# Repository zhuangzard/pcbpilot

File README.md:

<h1 align="center">pcbpilot</h1>

<p align="center">
  让 AI 直接操作嘉立创 EDA 专业版：读数据手册、画原理图、布局 PCB、整理丝印并完成检查。
</p>

<p align="center">
  <a href="https://github.com/zhuangzard/pcbpilot"><b>GitHub</b></a> ·
  <a href="docs/manual.md"><b>使用手册</b></a> ·
  <a href="docs/quick-start.md"><b>快速开始</b></a> ·
  <a href="README.en.md">English</a>
</p>

> **致谢与来源**：pcbpilot 由 [zhoushoujianwork/easyeda-agent](https://github.com/zhoushoujianwork/easyeda-agent)
> 分叉发展而来。CLI、daemon、连接器、typed action 体系、Skill、块库和大部分文档都出自原项目，
> 原作者与所有贡献者的提交历史完整保留在本仓库中，许可证为 MIT。衷心感谢原作者的工作。
> pcbpilot 在此基础上独立演进（首个新增能力是 `pcb auto` 电气感知整板自动设计引擎），
> 使用独立的命令名、端口段（61832–61841）、插件 uuid 与更新渠道，可与原版同时安装。

`pcbpilot` 是 EasyEDA Pro（嘉立创 EDA 专业版）的 AI 自动化层。你可以直接描述想做的
电路或要修的问题，Agent 会读取真实工程数据，通过官方 `eda.*` API 完成操作，并在写入前后
检查器件身份、引脚网络、几何、DRC 和保存状态。支持 **V3（3.2.x）与 V4**、桌面版与 Web 版、
国际版（pro.easyeda.com）与国内版（lceda.cn）。

## 它能做什么

| 使用场景 | 能力 |
|---|---|
| **拿 PDF / 尺寸图建库** | 读取型号、引脚和封装证据，创建 Symbol、Footprint、Device 和可选 3D Model；校验来源、焊盘依据和 pin↔pad 映射。[实战：AS07 私有库与框外丝印](docs/examples/as07-m1101d-sma/README.md) |
| **从需求做到一块板** | 从自然语言需求完成选型、原理图、分区布局、PCB、板框、叠层、布线、铺铜、丝印、DRC 和制造检查 |
| **原理图器件标准化** | 用 LCSC C 号或准确型号替换非标准器件，保留位号、位置和 PCB 同步身份；报告引脚差异并指导重新接线 |
| **原理图整理与修复** | 读取完整连接图，检查悬空、短路、跨页网名、NC、位号和模块归属，重新排版并回读验证 |
| **PCB 布局与布线** | `pcb auto` 整板引擎：机械约束 → 最小可行板框 → 原理图模块归属驱动的布局 → 多层协商布线 → 电源平面/分区铺铜 → 独立 DRC；天线净空、孔距、差分对、开关电源热回路 |
| **丝印调整** | 自动避开焊盘、器件体、禁区、板框和其他标签；添加板注、接口名、LED 极性及 SVG Logo |
| **复用成熟电路** | 从内置电路块库复用 CH340、ESP32 自动下载、按键、USB Hub、降压等拓扑，放件、连线并对账 |
| **电气分析与设计意图（v0.5）** | 从原理图做直流电源仿真（每脚电流、稳压器工作点、纹波），推导每个功能块的用途、每个网的电压/电流/线宽/过孔/间距/阻抗和网络类，写进 EasyEDA 规则与原理图注释；高压按 IEC 62368-1 / 60601-1（MOOP/MOPP）/ 61010-1 算爬电、间隙与开槽 |
| **检查与交付** | 原理图连接与几何检查、PCB DRC/DFM、BOM、网表、制造文件、截图、审计日志和显式保存；**每次运行自动生成版本化的设计报告**（仿真图表、器件可行性、工程计算、测试点、制造与上电注意事项），可直接交付客户 |

完整能力与状态见 [功能清单](docs/FEATURES.md)，命令索引见
[原理图 CLI](docs/cli/schematic.md) 和 [PCB CLI](docs/cli/pcb.md)。

## v0.5：从原理图到交付报告的电气闭环

以前原理图到 PCB 之间只传“位置”，PCB 不知道每个电路是做什么的、流多大电流、要多高的安规。
v0.5 把原理图里的电气意图算出来，一路带到布线、检查和交付：

```text
原理图 ──▶ sim power（直流仿真）──▶ intent derive（设计意图）──┬─▶ sch intent-annotate（写回原理图注释）
                                                             ├─▶ pcb rules apply（写入 EasyEDA 网络类/线宽/间距/差分对规则）
                                                             └─▶ pcb auto run --intent --sim
                                                                   ├─ 按段电流定线宽、布线后 IR 压降校核
                                                                   ├─ 高压：按标准的爬电/间隙、隔离带、自动开槽
                                                                   ├─ 高速：阻抗、对内/组内等长、参考平面
                                                                   └─ feedback.json：布线难点回推原理图（换脚等）
                                                                            ──▶ report design（版本化设计报告）
```

```bash
pcbpilot sim power      --project <工程> --pages <p1>,<p2> --out sim.json --report sim.md
pcbpilot intent derive  --project <工程> --pages <p1>,<p2> --out intent.json --report-dir reports/<项目>
pcbpilot sch intent-annotate --project <工程> --page <p1> --intent intent.json
pcbpilot pcb rules apply --project <工程> --doc <PCB> --intent intent.json      # 先 --dry-run
pcbpilot pcb auto run --board board.json --intent intent.json --sim sim.json --place --report-dir reports/<项目>
```

2026-09-27 这条链在 EasyEDA 桌面版 V3 上对 ESP32-S3 四层板完整实跑：规则写入并保存重载后仍同步，
布线 30/30、平面连接 52/52、各电源轨 IR 压降在预算内，原生 DRC 通过。高压（反激、医疗 2×MOPP、
CAT III 600 V、400 V 逆变）与高速（USB3、HDMI、PCIe、千兆以太网、DDR）压力测试的现状与已知缺口见
[高压隔离](.agents/skills/pcbpilot/references/recipes/hv-isolation.md) 与
[高速](.agents/skills/pcbpilot/references/recipes/high-speed.md) 配方。

### v0.6：设计前仿真 + 设计后仿真 + 板边安全距离

- **设计前**：`sim power`（电源树直流仿真）、`sim analog`（模拟电路 ngspice 仿真并按结果改元件值，改值需确认）、
  `intent derive`（线宽、**按电流定尺寸与数量的过孔**、间距、阻抗、**板边安全距离**）。
- **设计后**：`sim post-layout` 在 EasyEDA 回读的**真实铜皮**上算每个负载脚的直流压降、每个过孔电流、电流密度、
  每层稳态温度图和器件板温，并给出该加宽的线段、拐角与过孔（手工布的板也能用）；可选 Elmer FEM 交叉校验。
- **板边安全距离**（所有板默认）：外层铜 ≥ 0.5 mm、内层平面 ≥ 0.76 mm，高压域按爬电/间隙；写入 EasyEDA 规则并由
  `pcb check` 按 ERROR 检查。安装 pcbpilot 时自动安装 ngspice 与 Elmer（`pcbpilot sim tools`）。

### v0.7：console 本地驾驶舱、美观度测量、核心安全修复

daemon 在 `http://127.0.0.1:61832/ui/` 提供本地网页（`pcbpilot console open`，令牌在 `~/.pcbpilot/console.token`，仅回环）：
**监控首页**实时显示 daemon（pid/运行时长/端口/自动保存/登录服务）、各组件版本对齐（CLI、Skill、MCP、每个窗口的 connector）、
EasyEDA 窗口、**系统做过的全部项目**（运行中/空闲/已结束、DRC 与报告结论、时长、最后错误，重启后保留）和实时动作流；
项目页有设计流程时间线（S0–P11，证据视图）、仿真轮次与差值、报告预览、资料库（拖放上传 + BM25 检索，`pcbpilot kb`）、
流程配置（`pcbpilot.project.json`，`pcbpilot project-config`，Skill 先读、跳过项写进报告）；`pcbpilot ask` 决策卡在页面上回答。
console 从不编辑 EDA 工程，写入仍只走 typed action。本地 Agent（Claude Code / Codex）桥接是 v0.8 计划。
设计与 API 见 [docs/console-design.md](docs/console-design.md)。

同版还有：`pcbpilot pcb aesthetics` 布局/布线美观度测量（含对称检测与风格档位，只报告不计分，排在安全/电气之后）；
核心修复——按电流的过孔阵列在每个换层处强制满足（不满足必报）、差分对成对布线与耦合/过孔对称检查、布局给差分对留通道、
隔离/爬电/板边/过孔这些安全修复不再受时间预算影响（做不到就判 **NOT DELIVERABLE** 并写明原因）、守护进程重启更可靠。

### v0.7.1：美观度生成（PCB + 原理图）与原生总线

PCB 布局美观阶段（对齐、朝向、等距、同构子电路对称复制，布线复核守护）与布通后美化（扇出射线化、入线沿焊盘轴、S 形消除、落格）；
原理图走线清理、长线改标签、虚拟总线泳道与**原生总线**（宿主只接受 `NAME[a:b]`，只画带序号的组，V3 3.2.149 现场验证）；
美观交换有界且必报（每项电气分 ≤0.5、布局最多 +1 过孔），安全/布通/DRC/问题条数零容忍；`project inspect-eprj3`、
`health.officialCli`、`api upstream-diff` 吸收嘉立创官方 CLI 的格式与 API 知识。

### 设计报告（每次运行自动更新，版本化交付客户）

`report design` 按固定模板生成单文件 HTML（图表内联，可离线打开、打印）+ Markdown + JSON，每次运行一个新版本
`reports/<项目>/vN/`，并写出与上一版的变化。章节：封面与总体结论 · 执行摘要与主要风险 · 设计意图 ·
电源仿真（各场景电流、功率平衡、电源树、稳压器工作点、纹波、模型可信度）· **器件可行性**（每个器件的
电压/电流/功率 vs 额定与余量，未知额定标“需数据手册”，不猜）· 工程计算（线宽、过孔、间距、阻抗、爬电，
附公式）· 布局与布线（截图、IR 压降、SI、隔离、回推建议）· 验证状态 · **测试点计划**（测哪里、期望值
± 公差、仪器与方法）· **制造与装配注意事项** · **上电调试流程** · 附录。

样例（今天 ESP32 现场实跑数据生成）：[v1 报告（Markdown）](docs/examples/esp32-mini-design-report/v1/report.md) ·
[单文件 HTML（下载后打开）](docs/examples/esp32-mini-design-report/v1/report.html) ·
[v1→v2 变更记录](docs/examples/esp32-mini-design-report/CHANGELOG.md) ·
模板与每节计算来源：[templates/design-report](.agents/skills/pcbpilot/templates/design-report/README.md) ·
使用说明：[design-report.md](.agents/skills/pcbpilot/references/design-report.md)。

## 直接这样告诉 Agent

安装完成后，不需要先学习 CLI。把需求和必要的文件交给支持 Skill 的 Agent，并明确使用
`pcbpilot`。

### 用 PDF 创建器件库

```text
请使用 pcbpilot，根据附件 ABC123.pdf 为完整型号 ABC123-QFN 建库。
先检查 EasyEDA 和 LCSC 库是否已有完全匹配的器件；没有再通读整份数据手册，核对订购
后缀、引脚表、封装尺寸图和推荐焊盘。自动创建 Symbol、Footprint 和 Device，保留证据页码，
先运行离线规格校验，再写入个人库。完成后回读 pin↔pad 映射并放置一个实例检查 Pin-1。
只有手册确实存在多个无法消歧的封装或缺少关键尺寸时再问我。
```

这个流程使用 `pcbpilot lib device validate --spec …` 在打开或修改 EasyEDA 前检查数据手册
证据、几何和引脚映射，再由 `lib device build` 创建完整资产。规格契约见
[数据手册驱动的自动建库](.agents/skills/pcbpilot/references/library-authoring.md)。

### 做一块 ESP32 最小系统板

```text
请使用 pcbpilot，在项目 ceshi 中完成一块 ESP32-S3-WROOM-1 最小系统板：
5V 端子输入，降压到 3V3，CH340 USB 下载，BOOT/RESET 按键，一颗 GPIO 控制的 LED，
四角 M3 固定孔。做 4 层板，GND 内电层，模组天线区域所有层 keepout。
请自行选型并核对数据手册，从原理图、布局、布线、铺铜、丝印一直做到 DRC 和保存完成。
```

完整实战与真实截图见
[一份需求文档 → ESP32-S3 四层板](docs/showcase-esp32-mini.md)。

### 调整当前 PCB 的丝印

```text
请使用 pcbpilot 检查当前 PCB 的全部位号和自由丝印。把压焊盘、超板框、重叠、
朝向不一致和底层未镜像的问题整理好；保留 LED 正负极、接口名称和必要板注。
完成后运行 pcb check 和官方 DRC，导出一张复核图并保存。
```

### 标准化原理图器件

```text
请使用 pcbpilot 扫描当前原理图，把无准确料号、非标准符号或封装不一致的器件列出来。
优先匹配标准器件库和准确 LCSC C 号，核对型号、封装及引脚后再替换。
替换时保留位号、位置和 uniqueId；如果 pinDiff 非空，修复接线并重新运行 sch check、
bridge-check 和官方 DRC。最后输出替换清单和仍无法确定的器件。
```

### 出一份交付客户的设计报告

```text
请使用 pcbpilot 给当前工程出设计报告：先对原理图做电源仿真和设计意图推导，再用已完成的布线结果、
保存重载后的回读、原生 DRC、pcb check、规则同步和逐焊盘对账作为证据，生成新版本的设计报告。
额定未知的器件标“需数据手册”，不要猜；总体结论里的每条警告写明取舍，告诉我相对上一版改了什么。
```

### 检查并修复已有工程

```text
请使用 pcbpilot 全面检查当前原理图和 PCB。先读取真实器件、引脚、网络、板框、叠层和
DRC 规则，再修复可以确定的问题。不要凭截图猜连接；所有修改完成后回读对账、运行连接/几何/DRC 检查、
保存，并把仍需人工决策的问题单独列出。
```

## 效果展示

### ESP32-S3 四层板：一句需求交给新 Agent，到 DRC 通过（v0.3.0，2026-09-25 实测）

输入只有 [esp32MiniRequire.md](esp32MiniRequire.md) 第一节的客户原始需求（不给 BOM、不给网表），交给一个
**没有任何上下文的新 Agent**，约 36 分钟自行完成：

- **原理图**：自行选型，画两页原理图（31 个器件、21 个网络，按功能模块加框），回读逐脚 0 差异，两页 strict gate 通过；
- **布局**：`pcb auto` 求出 53.5 × 39.5 mm 的最小板框，四角 M3，ESP32 天线独占上边并全层禁布，USB-C 贴下边外伸
  0.5 mm；原理图模块框决定 PCB 归属（降压电容跟降压芯片、EN 复位电容贴 EN 脚、ESD 贴 USB 口）；两轮自检
  （第 2 轮保存 → 重载 → 重读 → 重新出图）后进入布线；
- **布线**：4 层（TOP / IN1 GND 平面 / IN2 电源分区 / BOTTOM），信号 30/30、平面连接 54/54，综合分 92.3；
  原生 DRC 通过、`pcb check` 0 ERROR、丝印无重叠、逐焊盘对账 0 差异、保存重开后内容哈希不变；
- **反哺工具**：这一轮暴露的 11 个问题（USB-C 封装定位孔未建模、USB 差分线跨电源分割、丝印不收敛、
  按工程名检查误报等）全部修进仓库，并在同一块板上现场复测通过，随 v0.3.0 发布；
- 宿主：EasyEDA Pro **V3 3.2.149 桌面版**（国际版）。

| 原理图第 1 页（USB-C / CH340C 串口与自动下载 / 5V 输入） | 原理图第 2 页（降压 / ESP32-S3 / 按键 / LED） |
|---|---|
|  |  |

| 布局（两轮自检后、布线前） | 布线 + 铺铜 + 丝印（终检通过） |
|---|---|
|  |  |

过程、问题与修法见 [pcb-auto 实测记录](.agents/skills/pcbpilot/references/pcb-auto.md#实测记录)。

## 上游 easyeda-agent 的案例（分叉前）

以下三个案例由原项目作者 [zhoushoujian](https://github.com/zhoushoujianwork) 在分叉前完成，保留在此作为能力来源的记录。

### 从模块尺寸图到个人私有库

**需求：** 按用户提供的 AS07-M1101D-SMA 尺寸与引脚图创建个人库，原理图保持双排引脚的
左右顺序；封装标注引脚名和型号，丝印全部放在模块覆盖区域外，安装后仍可查看，并收紧、对齐。

**结果：** 已创建并保存 Symbol、Footprint 和 Device，核对 8 个引脚与 8 个通孔焊盘映射；
修正符号边框闭合和引脚方向。封装左侧用两列脚号＋名称，列间距约 0.5 mm，靠框一列距框
约 0.6 mm；型号居中放在框外上方，实际文字包围盒回读无重叠。
最终按用户要求使用普通引脚线和未定义类型，1 脚使用独立圆形标记；保留用户清理 NC 后的状态。

这次输入是用户尺寸图，不是完整原厂 PDF；焊盘与部分偏移采用明确假设计算。
尚未验证实物装配、放置实例和 PCB DRC，不作为生产就绪证明。
[查看原始需求图、封装预览、规格与回读结果](docs/examples/as07-m1101d-sma/README.md)。

### 嘉立创 PCB 初级考试第十八期：AT32F415 Layout

当前参数化 Layout 基线包含 69 个器件、15 个功能区和 90 × 50 mm 圆角板框，用于验证
“样例关系 → 算法候选 → AI 选择 → typed 写入 → 回读”的布局方法。该图展示布局阶段结果，
不代表整板布线或生产检查已经完成。

标准考试来源：**嘉立创 PCB 初级考试题第十八期**。执行步骤、参数和验证边界见
[260919 AT32F415 考试执行指导](docs/260919-exam-execution-guide.md)。

### 数据驱动的原理图组合

Agent 先在本地连接数据中核对器件、引脚和网络，再计算模块内部布局并写回 EasyEDA；粉色虚线框
表示独立功能区，Apply 后逐脚回读，而不是仅凭截图判断成功。

## 安装与开始使用

pcbpilot 由四部分组成：`pcbpilot` CLI/daemon、运行在 EasyEDA 内的 **PCB Pilot Connector**
（`.eext`，侧载安装，不在插件市场）、AI 客户端里的 `pcbpilot` Skill，以及可选的 MCP 服务。

### 新机器：一句话交给 Claude

```text
克隆 https://github.com/zhuangzard/pcbpilot 并按仓库 AGENTS.md 的「新机器安装」完成 pcbpilot 安装，
最后告诉我需要我手动做的连接器导入步骤。
```

Agent 会运行 [`scripts/setup-agent.sh`](scripts/setup-agent.sh)：编译 CLI，为 **Claude Code / Codex / ZCode**
链接 Skill 并注册 MCP，构建连接器，把 daemon 装成开机登录自动启动的服务（必需，`pcbpilot daemon service install`），最后自动验证（MCP 真实握手）。若机器上装过上游
easyeda-agent，会移除其 MCP 并把其 Skill 移入可恢复的备份，避免与 pcbpilot 争用同类任务。也可以自己运行：

```bash
git clone https://github.com/zhuangzard/pcbpilot.git && cd pcbpilot
scripts/setup-agent.sh          # --dry-run 先预览；无 Go 时自动改用发布版
```

只装已发布版本（无需克隆）：

```bash
curl -fsSL https://raw.githubusercontent.com/zhuangzard/pcbpilot/main/install.sh | bash      # macOS / Linux
irm https://raw.githubusercontent.com/zhuangzard/pcbpilot/main/install.ps1 | iex             # Windows PowerShell
```

三种安装方式都会顺带执行 `pcbpilot sim tools install --yes`，自动安装开源仿真工具：**ngspice**（必需，
`sim power --spice-check` 与模拟 SPICE 流程）和 **Elmer FEM**（可选热交叉验证；macOS 走官方 Homebrew tap
源码编译，较慢，失败只警告）。pcbpilot 自带的仿真器已编译进二进制，无需安装。`pcbpilot sim tools check`
查看状态；`--no-sim-tools` / `PCBPILOT_SIM_TOOLS=0` 跳过。各平台命令见 [使用手册 3.4](docs/manual.md#34-仿真工具)。

### 唯一的人工步骤：导入连接器

1. EasyEDA Pro → 扩展管理器 → 已安装：先**卸载**旧的 “PCB Pilot Connector”（同 uuid 不卸载会静默导入失败）；
2. 导入 `setup-agent.sh` 打印的 `.eext`，或 [Release](https://github.com/zhuangzard/pcbpilot/releases/latest) 里的 `pcbpilot-connector.eext`；
3. **高级 → 扩展管理器 → 已安装 → 选中 PCB Pilot Connector**（状态须为 `Enabled`）→ **Config** 页签 → 勾选 **允许外部交互**；
4. 重新加载编辑器（Web 刷新页面，桌面重开工程），然后：

```bash
pcbpilot health        # windows[] 出现你的工程和文档，connectorVersion 与仓库一致
```

**升级是自动的**：daemon 定期检查 GitHub，在 EasyEDA 空闲时升级 CLI、Skill、MCP 和仿真工具（失败自动
回滚，`pcbpilot update --auto off` 可关闭）；手动一步：`pcbpilot update`（`--check` 只看，`--rollback` 回退）。
连接器版本必须与 CLI 一致，daemon 会把新 `.eext` 下载到 `~/.pcbpilot/connector/`，按上面 3 步重导即可。

完整安装、升级、MCP、排障见 **[使用手册](docs/manual.md)**。

## 为什么它适合 Agent

直接把任意 JavaScript 丢进编辑器很难审查，也难确认部分失败。pcbpilot 把常用能力封装成
有明确输入输出的 typed actions，并在工作流中加入：

- 写入前检查目标工程、页面、器件身份和源数据；
- 写入后回读引脚、网络、几何和对象绑定；
- 原理图 `layout-lint → check → bridge-check → DRC` 分项报告事实与差异；
- PCB 使用真实 DRC 规则完成布局、布线、铺铜和制造检查；
- 对部分成功、超时和无法确认的结果停止盲目重试；
- 自动保存作为安全网，关键节点仍显式保存。

```text
AI Agent / Skill
       │
       ▼
pcbpilot CLI + local daemon
       │ typed actions / audit / artifacts
       ▼
PCB Pilot Connector (.eext)
       │ official eda.* API
       ▼
EasyEDA Pro project
```

架构与协议细节见 [架构说明](docs/architecture.md) 和 [协议说明](docs/protocol.md)。

## 能力边界

- `pcb auto` 对中小型板可整板布通（ESP32 实测 100%）；大型 BGA 板（RK3568/K230 级）离线回归布通率 55–62%，
  适合作为起点，可选接外部 Freerouting。
- 连接器导入与“允许外部交互”需要人来做；Agent 不操作 EDA 的 GUI。
- EasyEDA 扩展 API 不提供编程式 undo，项目通过源数据、写前守卫、回读和失败回滚降低风险。
- 受控阻抗所需的介质厚度、Er 和铜厚无法从当前 `eda.*` API 完整读取，不能自动声称阻抗合格。
- PDF 自动建库仍以具体型号和原厂证据为准；扫描模糊、封装后缀不明或缺少焊盘依据时会暂停询问。

当前能力与边界见 [功能清单](docs/FEATURES.md) 和 [CLI 索引](docs/cli/README.md)。
过往调研和实测结果集中在 [历史证据索引](docs/reviews/README.md)。

## 开发与贡献

- 文档导航与信息归属：[docs/README.md](docs/README.md)
- 跨项目查询、维护 Skill 和多客户端兼容：[Agent 协作设计](docs/agent-collaboration.md)
- 开发环境：[docs/dev-environment.md](docs/dev-environment.md)
- 电路块贡献：[standard-blocks-contributing.md](.agents/skills/pcbpilot/references/standard-blocks-contributing.md)
- Skill 入口：[.agents/skills/pcbpilot/SKILL.md](.agents/skills/pcbpilot/SKILL.md)
- 仓库结构与开发约定：[AGENTS.md](AGENTS.md)

感谢嘉立创 EDA 专业版开放扩展接口，也感谢
[@jlceda/pro-api-types](https://www.npmjs.com/package/@jlceda/pro-api-types)、
[Freerouting](https://github.com/freerouting/freerouting) 及
[EasyEDA 官方开源扩展](https://github.com/easyeda) 提供的基础与参考。

## 许可证

[MIT](LICENSE)。`extension/src/beautify/` 中移植自
[Easy_EDA_PCB_Beautify](https://github.com/m-RNA/Easy_EDA_PCB_Beautify) 的文件沿用
Apache-2.0，详见 [NOTICE](NOTICE)。

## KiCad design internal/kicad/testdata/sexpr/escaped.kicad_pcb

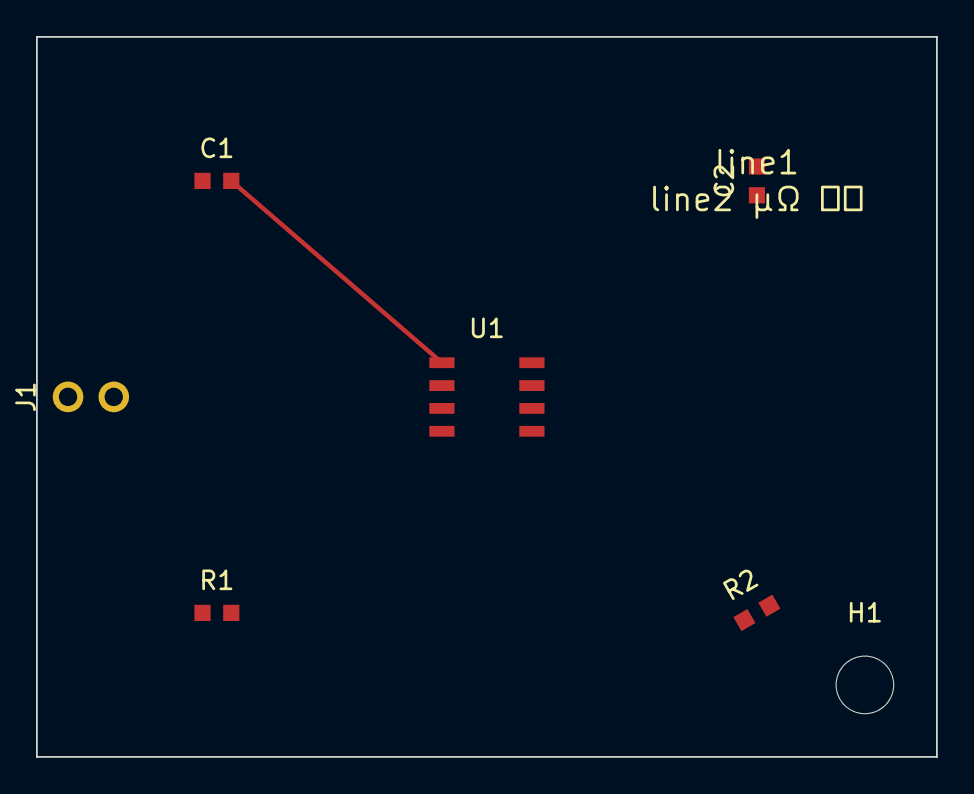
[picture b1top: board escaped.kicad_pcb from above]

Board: 2 copper layers, 50.0 x 40.0 mm, 8 parts (1 on the bottom side), 6 nets.

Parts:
C1: C1; C0603
C2: 10k "1%" C:\lib; C0603
H1: H1; MountingHole_3.2mm_M3
J1: J1; Header1x02
R1: R1; R0603
R2: R2; R0603
R3: R3; R0603
U1: U1; IC8

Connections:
A: R1.1, R3.1, U1.2
B: R2.1, U1.3
C: R1.2, U1.5
D: R2.2, U1.6
GND: C1.2, C2.2, J1.2, R3.2, U1.4, U1.8
VCC: C1.1, C2.1, J1.1, U1.1, U1.7
